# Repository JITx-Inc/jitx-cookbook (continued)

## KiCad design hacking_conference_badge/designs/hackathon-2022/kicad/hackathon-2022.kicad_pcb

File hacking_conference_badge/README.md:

# Hacking Conference Badge

This recipe serves as a playground for you to learn JITX while working on a functional PCB design. You’ll use the electronic conference badge template design in this folder to design your own electronic badge.

This template is a fully functioning board with an RP2040 microcontroller, battery and USB power solution, and a number of peripheral input/output devices that you can use as part of your badge design. We can roughly separate the template badge into 2 parts - the subsystems that you won’t change, and those that you (likely) will change.

##### Won't Change

- MCU (RP2040)
- MCU supporting circuitry (flash, crystal, etc.)
- power system (USB, battery charger, battery port, power switch)

##### Will Change

- RGB LED array
- solid color LED array
- potentiometers (dials/knobs)
- key-matrix array (buttons)
- Speaker
- TOF sensor (distance sensor)
- WS2816 array (addressable RGB LEDs)

### How The Badge Works

At this point, you should have forked/cloned this repo board, updated/inited submodules, and opened this folder/project in JITX VSCode. Make sure you're running the latest JITX version in VSCode.

The main design of the board is in `main.stanza`, open that in JITX VSCode and press "Ctrl+Enter" to build the board.

##### The Code

Briefly, let's go through the code.

The top level module is `public pcb-module hacking_conference_badge_module :`

Here, we instantiate and connect everything that will be part of our board.

`usb` - the USB connector
`battery` - the JST connector for the LiPo battery
`sw` - the power switch in series with the BQ2407 battery charger
`ld` - the LDO power/voltage regulator that converts voltage from the battery charger output to 2.8V for the RP2040 and other peripherals to run off of
`rpi` - the RP2040 microcontroller -> the brains/compute of the board
`led-drive` - the LED driver -> this accepts commands over I2C and turns the attached LEDs on/off. Notice that the RGB LEDs on the top left of the board are connected to this with 3 connections each - that is 1 for Red, 1 for green, and 1 for blue
`led-driver-shifter` - logic level shifter for the LED-driver. The LED-driver logic is running at its input power (~4.2V) whereas the RP2040 logic is running at 2.8V. This driver shifter shifts between those voltage levels so the LED-driver and RP2040 can talk to each other
`en-sw` - there are two of these which turn on and off a bank of single-color LEDs
`rgb-grid` - grid of RGB LEDs connected to the LED-driver
`amp` - this is the audio amplifier and speaker submodule
`knobs` - knobs/dials/potentiometers you can read directly with the RP2040 and use to do arbitrary things
`tof` - time of flight distance sensor, talks to RP2040 with I2C
`indicator-led-array` - array of WS2816 RGB addressable LEDs
`geom(NET)` - these are ground and power plane/pours
`power-net-class` - setting the trace width for various nets in the design
`run-design` - this compiles the board, or it runs checks on the board (depending on arguments)

##### Happy Hacking!

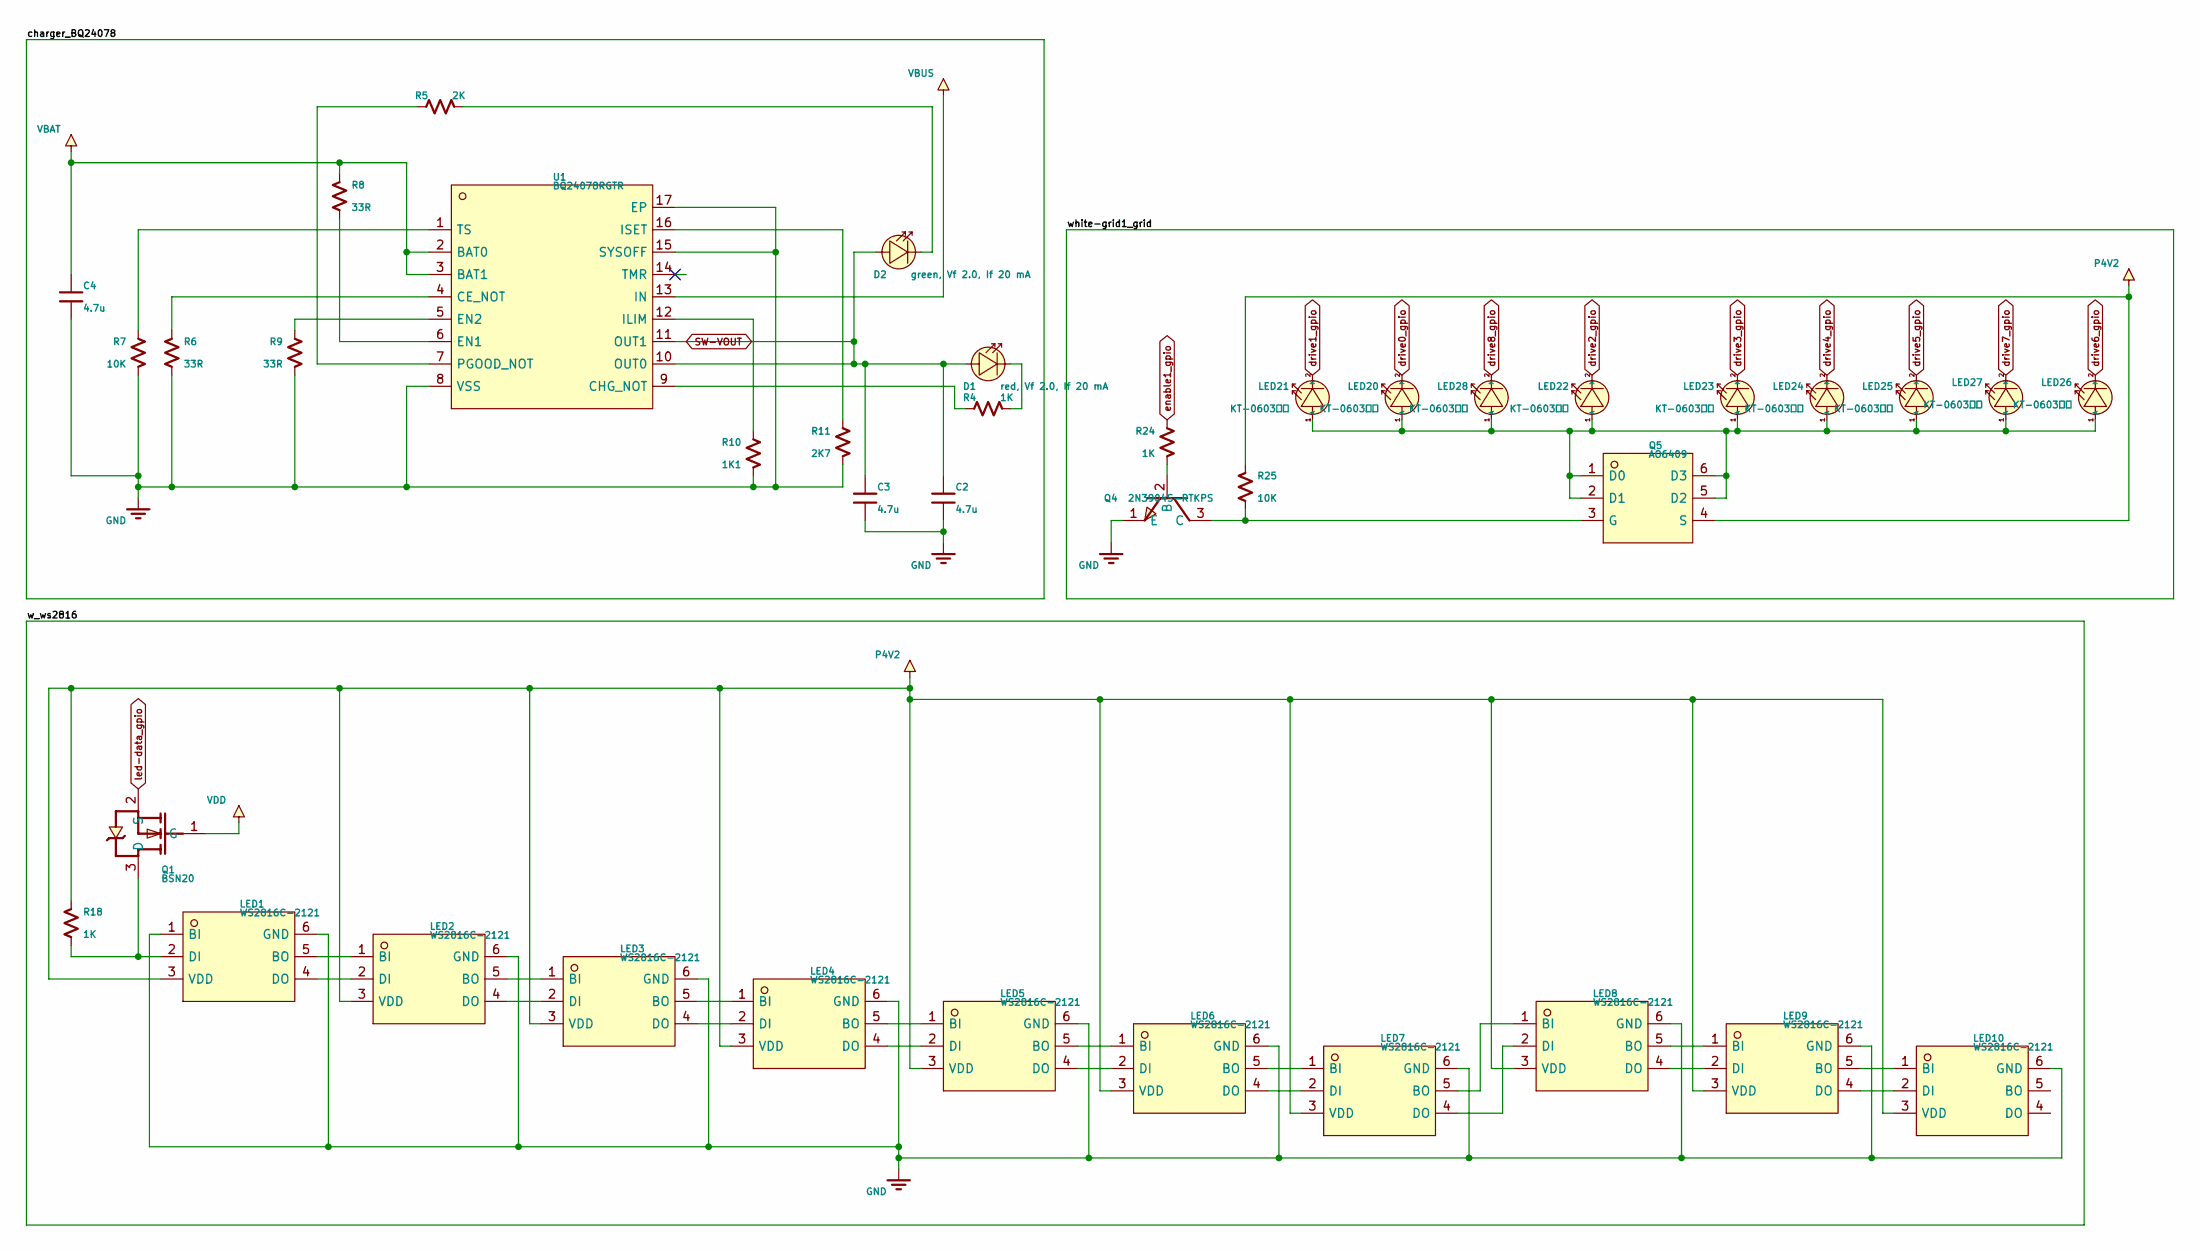
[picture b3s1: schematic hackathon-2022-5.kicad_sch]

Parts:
C2, C3, C4: 4.7u; Pkg0402; MPN 0402YD475MAT2A
D1: red, Vf 2.0, If 20 mA; Pkg0603; MPN red, Vf 2.0, If 20 mA
D2: green, Vf 2.0, If 20 mA; Pkg0603; MPN green, Vf 2.0, If 20 mA
LED1, LED2, LED3, LED4, LED5, LED6, LED7, LED8, LED9, LED10: WS2816C-2121; LED_SMD_6P_L2_2_W2_2_TL_1; MPN WS2816C-2121; LCSC C965561
LED20, LED21, LED22, LED23, LED24, LED25, LED26, LED27, LED28: KT-0603白灯; LED0603_R_RD_WHITE; MPN KT-0603白灯; LCSC C2290
Q1: BSN20; SOT_23_3_L2_9_W1_6_P1_90_LS2_8_BR; MPN BSN20; LCSC C116157
Q4: 2N3904S-RTKPS; SOT_23_3_L2_9_W1_3_P1_90_LS2_4_TR; MPN 2N3904S-RTKPS; LCSC C18536
Q5: AO6409; TSOP_6_L3_0_W1_5_P0_95_LS2_8_BR; MPN AO6409; LCSC C115833
R4: 1K; Pkg0402_6
R5: 2K; Pkg0402_6
R6, R8, R9: 33R; Pkg0402_6
R7: 10K; Pkg0402_6
R10: 1K1; Pkg0402_4; MPN RT0402DRE071K1L
R11: 2K7; Pkg0402_1; MPN RK73B1ERTTP272J
R18: 1K; Pkg0402_4; MPN RT0402BRB071KL
R24: 1K; Pkg0402_1; MPN SG73P1EWTTP1001F
R25: 10K; Pkg0402_1; MPN RC1005F103CS
U1: BQ24078RGTR; VQFN_16_L3_0_W3_0_P0_50_BL_EP; MPN BQ24078RGTR; LCSC C473396

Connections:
GND: C2.2, C3.2, C4.2, LED1.1 (BI), LED1.6 (GND), LED2.6 (GND), LED3.6 (GND), LED4.6 (GND), LED5.6 (GND), LED6.6 (GND), LED7.6 (GND), LED8.6 (GND), LED9.6 (GND), LED10.6 (GND), Q4.1 (E), R6.1, R7.2, R9.2, R10.2, R11.2, U1.8 (VSS), U1.15 (SYSOFF), U1.17 (EP); also elsewhere on the board
unnamed: D1.c, R4.2
unnamed: D2.c, R5.2
unnamed: LED1.5 (BO), LED2.1 (BI)
unnamed: LED1.2 (DI), Q1.3 (D), R18.1
unnamed: LED1.4 (DO), LED2.2 (DI)
unnamed: LED2.5 (BO), LED3.1 (BI)
unnamed: LED2.4 (DO), LED3.2 (DI)
unnamed: LED3.5 (BO), LED4.1 (BI)
unnamed: LED3.4 (DO), LED4.2 (DI)
unnamed: LED4.5 (BO), LED5.1 (BI)
unnamed: LED4.4 (DO), LED5.2 (DI)
unnamed: LED5.5 (BO), LED6.1 (BI)
unnamed: LED5.4 (DO), LED6.2 (DI)
unnamed: LED6.5 (BO), LED7.1 (BI)
unnamed: LED6.4 (DO), LED7.2 (DI)
unnamed: LED7.5 (BO), LED8.1 (BI)
unnamed: LED7.4 (DO), LED8.2 (DI)
unnamed: LED8.5 (BO), LED9.1 (BI)
unnamed: LED8.4 (DO), LED9.2 (DI)
unnamed: LED9.5 (BO), LED10.1 (BI)
unnamed: LED9.4 (DO), LED10.2 (DI)
unnamed: LED20.1 (A), LED21.1 (A), LED22.1 (A), LED23.1 (A), LED24.1 (A), LED25.1 (A), LED26.1 (A), LED27.1 (A), LED28.1 (A), Q5.1 (D0), Q5.2 (D1), Q5.5 (D2), Q5.6 (D3)
unnamed: Q4.2 (B), R24.2
unnamed: Q4.3 (C), Q5.3 (G), R25.1
unnamed: R6.2, U1.4 (CE_NOT)
unnamed: R4.1, U1.9 (CHG_NOT)
unnamed: R8.1, U1.6 (EN1)
unnamed: R9.1, U1.5 (EN2)
unnamed: R10.1, U1.12 (ILIM)
unnamed: R11.1, U1.16 (ISET)
unnamed: R5.1, U1.7 (PGOOD_NOT)
unnamed: R7.1, U1.1 (TS)
P4V2: LED1.3 (VDD), LED2.3 (VDD), LED3.3 (VDD), LED4.3 (VDD), LED5.3 (VDD), LED6.3 (VDD), LED7.3 (VDD), LED8.3 (VDD), LED9.3 (VDD), LED10.3 (VDD), Q5.4 (S), R18.2, R25.2; also elsewhere on the board
SW-VOUT: C2.1, C3.1, D1.a, D2.a, U1.10 (OUT0), U1.11 (OUT1); also elsewhere on the board
VBAT: C4.1, R8.2, U1.2 (BAT0), U1.3 (BAT1); also elsewhere on the board
VBUS: U1.13 (IN); also elsewhere on the board
VDD: Q1.1 (G); also elsewhere on the board
drive0_gpio: LED20.2 (K); also elsewhere on the board
drive1_gpio: LED21.2 (K); also elsewhere on the board
drive2_gpio: LED22.2 (K); also elsewhere on the board
drive3_gpio: LED23.2 (K); also elsewhere on the board
drive4_gpio: LED24.2 (K); also elsewhere on the board
drive5_gpio: LED25.2 (K); also elsewhere on the board
drive6_gpio: LED26.2 (K); also elsewhere on the board
drive7_gpio: LED27.2 (K); also elsewhere on the board
drive8_gpio: LED28.2 (K); also elsewhere on the board
enable1_gpio: R24.1; also elsewhere on the board
led-data_gpio: Q1.2 (S); also elsewhere on the board

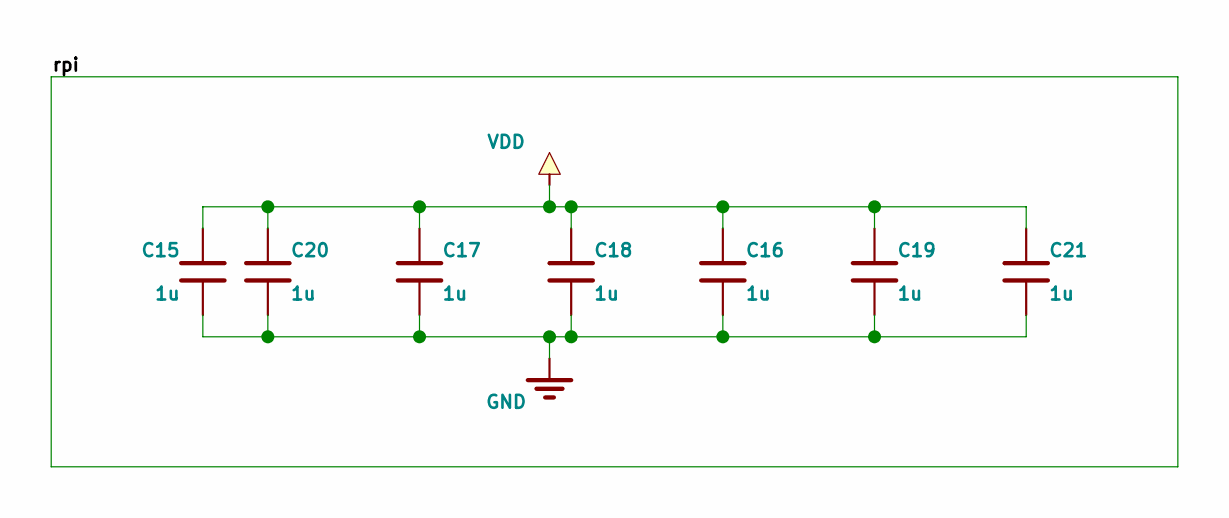
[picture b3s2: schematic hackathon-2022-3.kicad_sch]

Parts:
C15, C16, C17, C18, C19, C20, C21: 1u; Pkg0402_2; MPN LMK105C6105KV-F

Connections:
GND: C15.1, C16.2, C17.2, C18.2, C19.2, C20.2, C21.2; also elsewhere on the board
VDD: C15.2, C16.1, C17.1, C18.1, C19.1, C20.1, C21.1; also elsewhere on the board

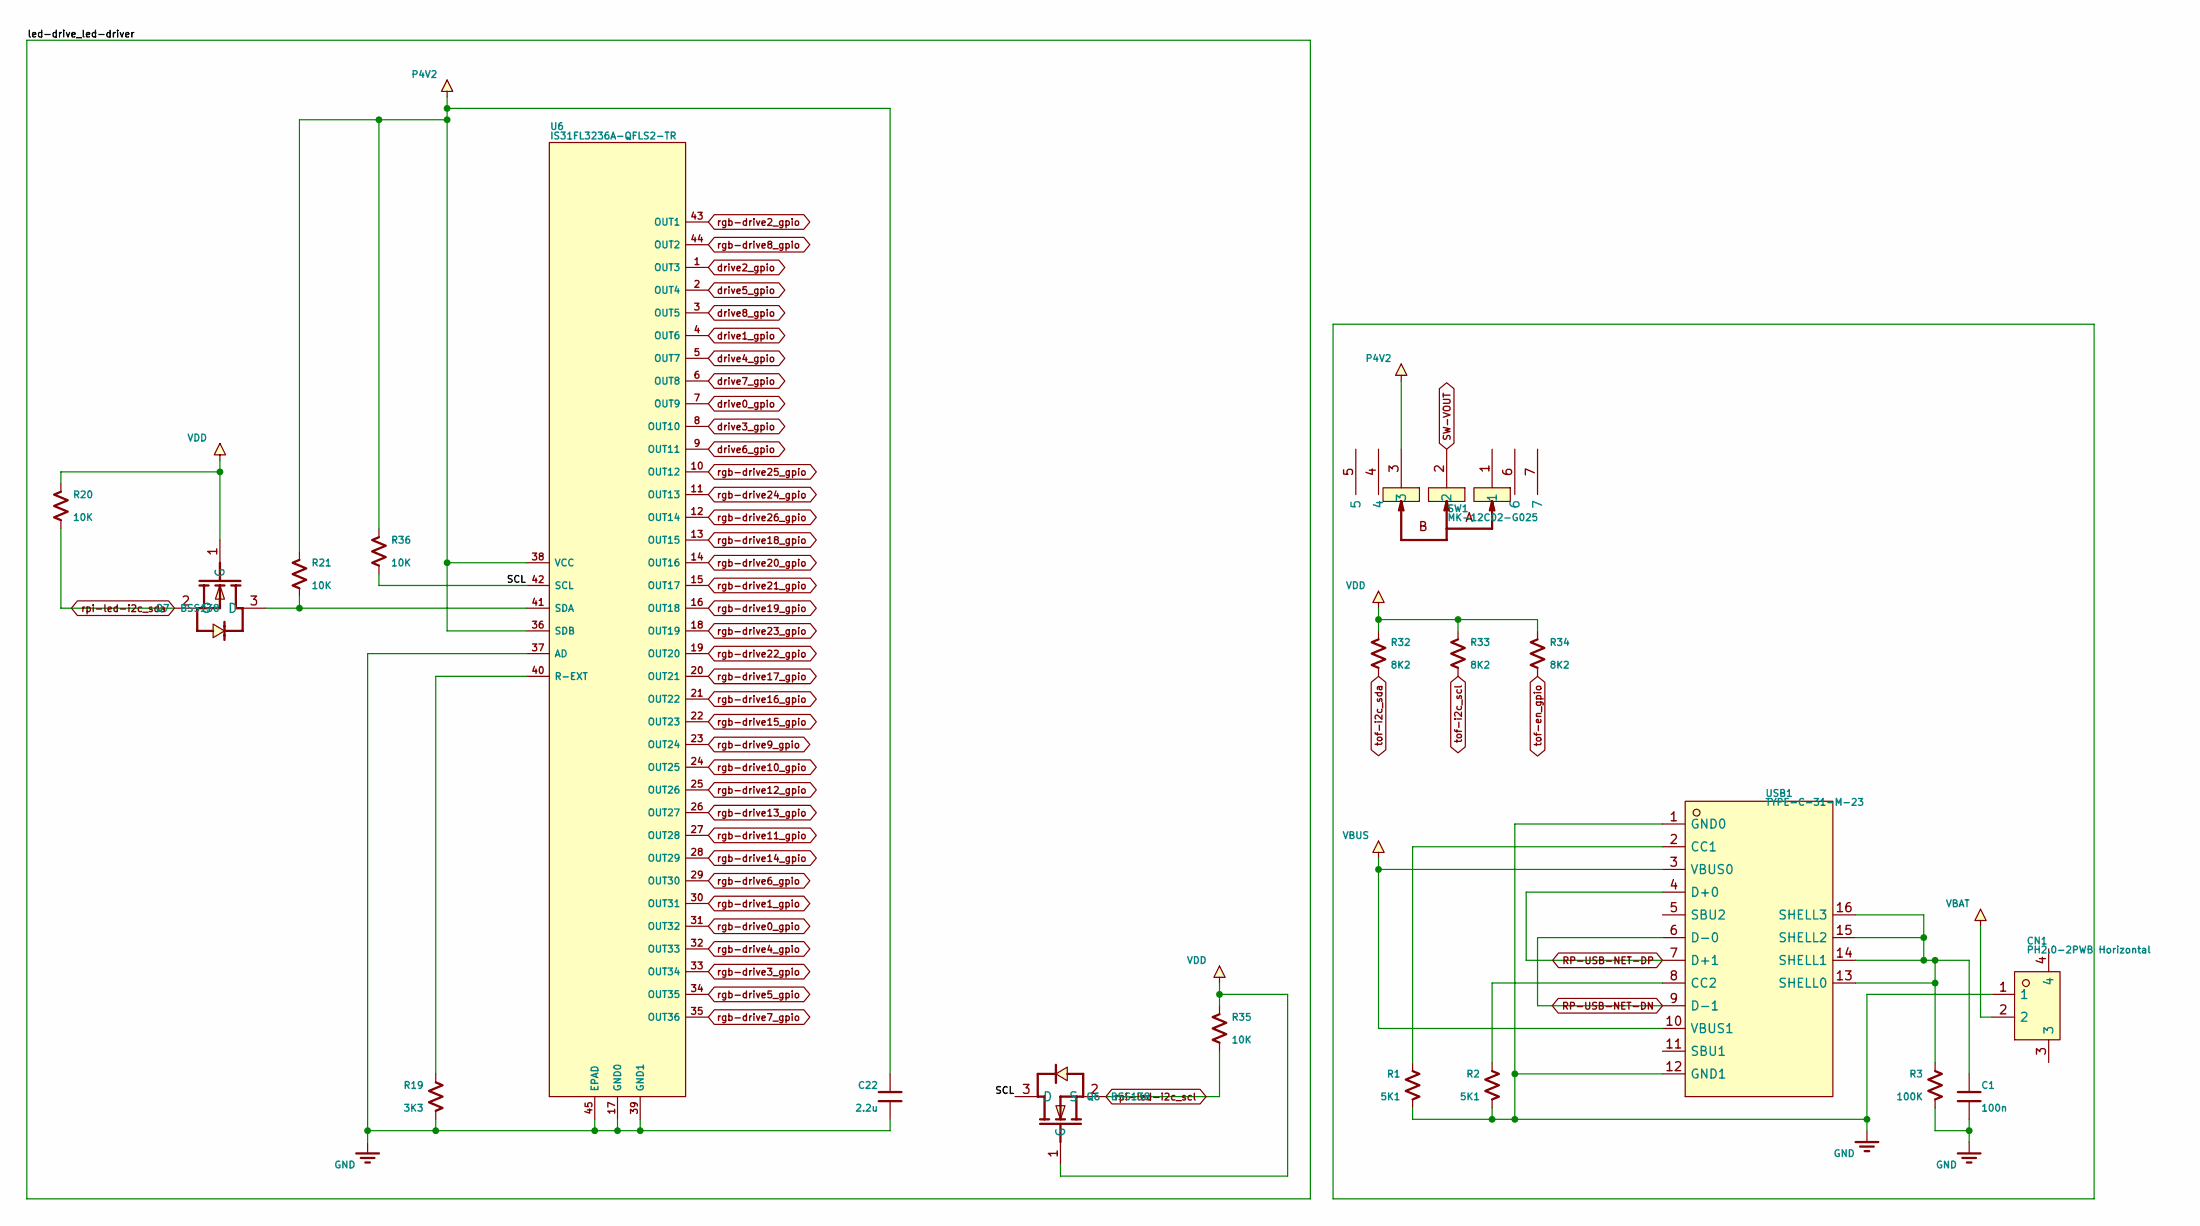
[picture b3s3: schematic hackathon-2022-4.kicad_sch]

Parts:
C1: 100n; Pkg0402_2; MPN CL05B104KA5NNNC
C22: 2.2u; Pkg0402_5; MPN C1005X5R1E225K050BE
CN1: PH2.0-2PWB Horizontal; CONN_SMD_2P_P2_00_PH2_0_SPWB; MPN PH2.0-2PWB Horizontal; LCSC C47647
Q6, Q7: BSS138; SOT_23_3_L2_9_W1_3_P1_90_LS2_4_BR; MPN BSS138; LCSC C713688
R1, R2: 5K1; Pkg0402_1; MPN ERJ-2GEJ512X
R3: 100K; Pkg0402_1; MPN RK73B1ERTTP104J
R19: 3K3; Pkg0402_1; MPN RK73H1ERTTP3301D
R20, R21, R35, R36: 10K; Pkg0402_1; MPN ESR01MZPJ103
R32, R33, R34: 8K2; Pkg0402_3; MPN CR0402AJW-822GLF
SW1: MK-12C02-G025; SW_SMD_MK_12C02_G025; MPN MK-12C02-G025; LCSC C778186
U6: IS31FL3236A-QFLS2-TR; C246443; MPN IS31FL3236A-QFLS2-TR; LCSC C246443
USB1: TYPE-C-31-M-23; USB_C_SMD_TYPE_C_31_M_23; MPN TYPE-C-31-M-23; LCSC C530613

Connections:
/4: led-drive_u/SCL: Q6.3 (D), R36.1, U6.42 (SCL)
GND: C1.2, C22.1, CN1.1, R1.2, R2.2, R3.2, R19.2, U6.17 (GND0), U6.37 (AD), U6.39 (GND1), U6.45 (EPAD), USB1.1 (GND0), USB1.12 (GND1); also elsewhere on the board
unnamed: Q7.3 (D), R21.1, U6.41 (SDA)
unnamed: R19.1, U6.40 (R-EXT)
unnamed: R1.1, USB1.2 (CC1)
unnamed: R2.1, USB1.8 (CC2)
unnamed: C1.1, R3.1, USB1.13 (SHELL0), USB1.14 (SHELL1), USB1.15 (SHELL2), USB1.16 (SHELL3)
P4V2: C22.2, R21.2, R36.2, SW1.3, U6.36 (SDB), U6.38 (VCC); also elsewhere on the board
RP-USB-NET-DN: USB1.6 (D-0), USB1.9 (D-1); also elsewhere on the board
RP-USB-NET-DP: USB1.4 (D+0), USB1.7 (D+1); also elsewhere on the board
SW-VOUT: SW1.2; also elsewhere on the board
VBAT: CN1.2; also elsewhere on the board
VBUS: USB1.3 (VBUS0), USB1.10 (VBUS1); also elsewhere on the board
VDD: Q6.1 (G), Q7.1 (G), R20.2, R32.2, R33.2, R34.2, R35.2; also elsewhere on the board
drive0_gpio: U6.7 (OUT9); also elsewhere on the board
drive1_gpio: U6.4 (OUT6); also elsewhere on the board
drive2_gpio: U6.1 (OUT3); also elsewhere on the board
drive3_gpio: U6.8 (OUT10); also elsewhere on the board
drive4_gpio: U6.5 (OUT7); also elsewhere on the board
drive5_gpio: U6.2 (OUT4); also elsewhere on the board
drive6_gpio: U6.9 (OUT11); also elsewhere on the board
drive7_gpio: U6.6 (OUT8); also elsewhere on the board
drive8_gpio: U6.3 (OUT5); also elsewhere on the board
rgb-drive0_gpio: U6.31 (OUT32); also elsewhere on the board
rgb-drive1_gpio: U6.30 (OUT31); also elsewhere on the board
rgb-drive2_gpio: U6.43 (OUT1); also elsewhere on the board
rgb-drive3_gpio: U6.33 (OUT34); also elsewhere on the board
rgb-drive4_gpio: U6.32 (OUT33); also elsewhere on the board
rgb-drive5_gpio: U6.34 (OUT35); also elsewhere on the board
rgb-drive6_gpio: U6.29 (OUT30); also elsewhere on the board
rgb-drive7_gpio: U6.35 (OUT36); also elsewhere on the board
rgb-drive8_gpio: U6.44 (OUT2); also elsewhere on the board
rgb-drive9_gpio: U6.23 (OUT24); also elsewhere on the board
rgb-drive10_gpio: U6.24 (OUT25); also elsewhere on the board
rgb-drive11_gpio: U6.27 (OUT28); also elsewhere on the board
rgb-drive12_gpio: U6.25 (OUT26); also elsewhere on the board
rgb-drive13_gpio: U6.26 (OUT27); also elsewhere on the board
rgb-drive14_gpio: U6.28 (OUT29); also elsewhere on the board
rgb-drive15_gpio: U6.22 (OUT23); also elsewhere on the board
rgb-drive16_gpio: U6.21 (OUT22); also elsewhere on the board
rgb-drive17_gpio: U6.20 (OUT21); also elsewhere on the board
rgb-drive18_gpio: U6.13 (OUT15); also elsewhere on the board
rgb-drive19_gpio: U6.16 (OUT18); also elsewhere on the board
rgb-drive20_gpio: U6.14 (OUT16); also elsewhere on the board
rgb-drive21_gpio: U6.15 (OUT17); also elsewhere on the board
rgb-drive22_gpio: U6.19 (OUT20); also elsewhere on the board
rgb-drive23_gpio: U6.18 (OUT19); also elsewhere on the board
rgb-drive24_gpio: U6.11 (OUT13); also elsewhere on the board
rgb-drive25_gpio: U6.10 (OUT12); also elsewhere on the board
rgb-drive26_gpio: U6.12 (OUT14); also elsewhere on the board
rpi-led-i2c_scl: Q6.2 (S), R35.1; also elsewhere on the board
rpi-led-i2c_sda: Q7.2 (S), R20.1; also elsewhere on the board
tof-en_gpio: R34.1; also elsewhere on the board
tof-i2c_scl: R33.1; also elsewhere on the board
tof-i2c_sda: R32.1; also elsewhere on the board

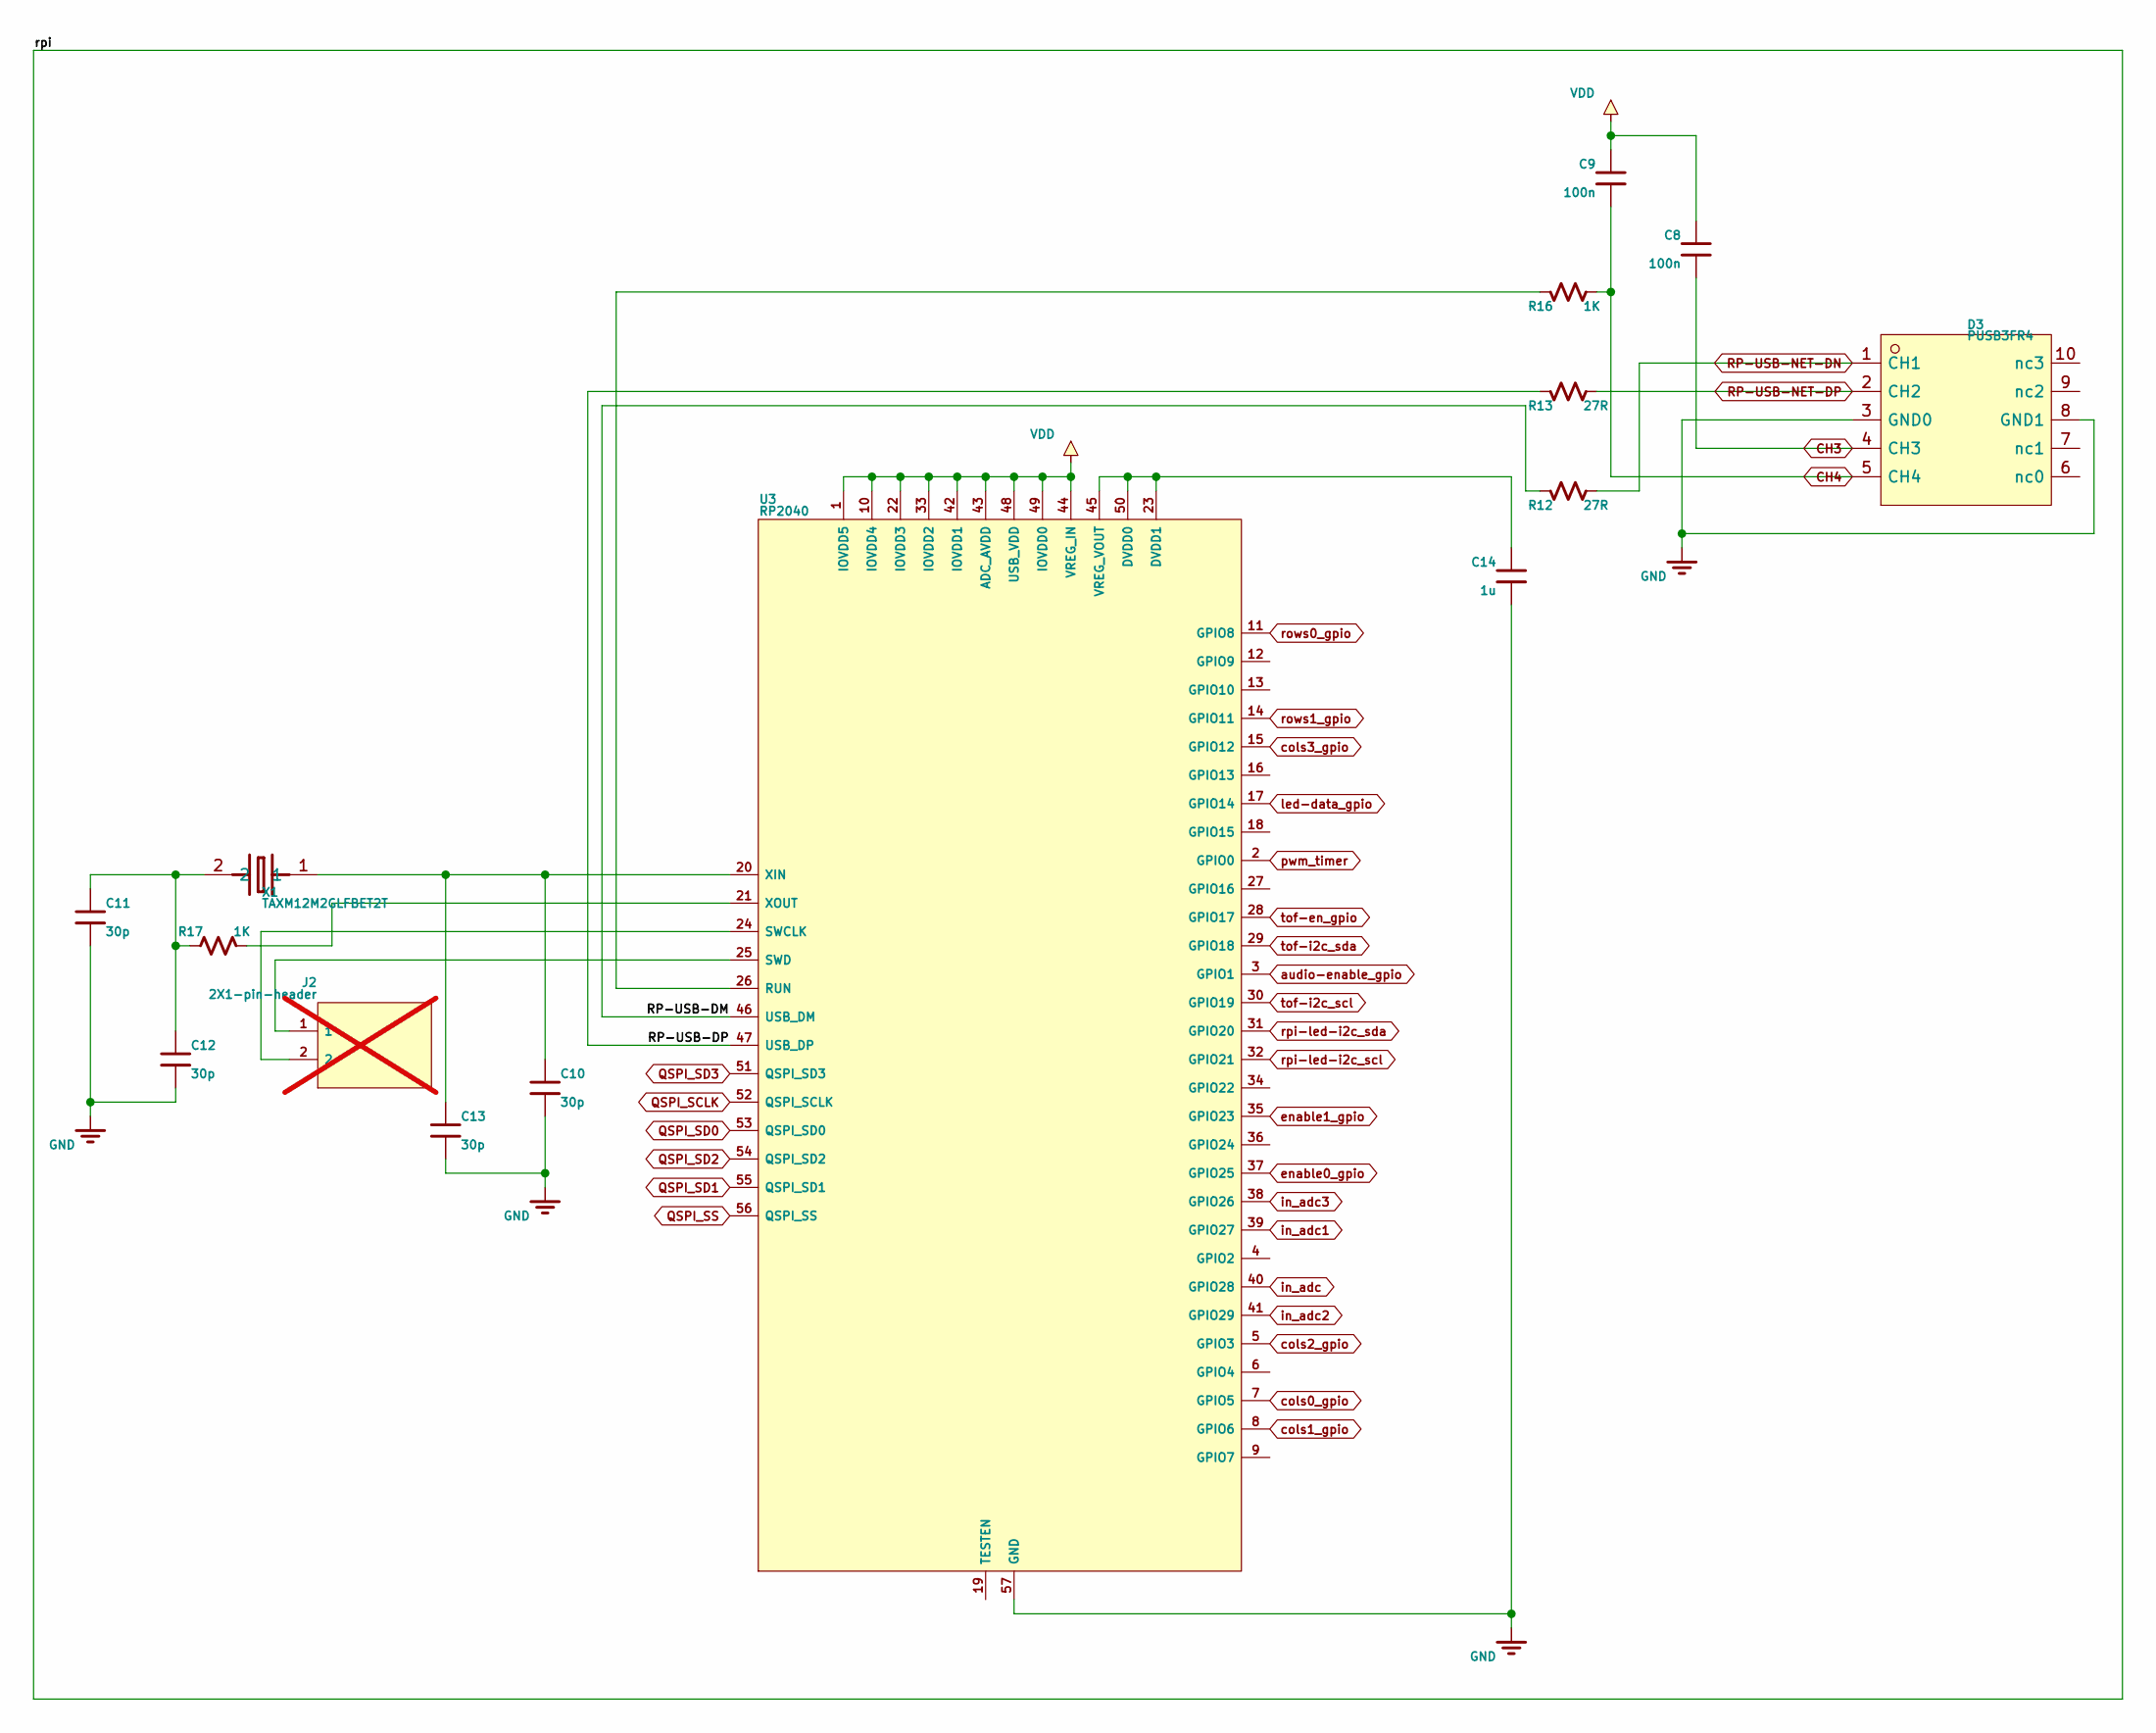
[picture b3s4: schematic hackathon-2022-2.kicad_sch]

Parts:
C8, C9: 100n; Pkg0402_2; MPN CL05B104KA5NNNC
C10, C11, C12, C13: 30p; Pkg0402_2; MPN CC0402JRNPO9BN300
C14: 1u; Pkg0402_2; MPN LMK105C6105KV-F
D3: PUSB3FR4; DFN2510A_10_L2_5_W1_0_P0_50_BL; MPN PUSB3FR4; LCSC C294620
J2: 2X1-pin-header; PIN_GRID; MPN 2X1-pin-header; not fitted
R12, R13: 27R; Pkg0402_1; MPN ERJ-U02F27R0X
R16, R17: 1K; Pkg0402_4; MPN RT0402BRB071KL
U3: RP2040; C2040; MPN RP2040
X1: TAXM12M2GLFBET2T; HC_49S_L11_4_W4_8; MPN TAXM12M2GLFBET2T; LCSC C111117

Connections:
/2: rpi_mcu/RP-USB-DM: R12.2, U3.46 (USB_DM)
/2: rpi_mcu/RP-USB-DP: R13.2, U3.47 (USB_DP)
CH3: C8.1, D3.4 (CH3); also elsewhere on the board
CH4: C9.1, D3.5 (CH4), R16.1; also elsewhere on the board
GND: C10.2, C11.2, C12.2, C13.2, C14.1, D3.3 (GND0), D3.8 (GND1), U3.57 (GND); also elsewhere on the board
unnamed: C11.1, C12.1, R17.1, X1.2
unnamed: C14.2, U3.23 (DVDD1), U3.45 (VREG_VOUT), U3.50 (DVDD0)
unnamed: R16.2, U3.26 (RUN)
unnamed: J2.2, U3.24 (SWCLK)
unnamed: J2.1, U3.25 (SWD)
unnamed: C10.1, C13.1, U3.20 (XIN), X1.1
unnamed: R17.2, U3.21 (XOUT)
QSPI_SCLK: U3.52 (QSPI_SCLK); also elsewhere on the board
QSPI_SD0: U3.53 (QSPI_SD0); also elsewhere on the board
QSPI_SD1: U3.55 (QSPI_SD1); also elsewhere on the board
QSPI_SD2: U3.54 (QSPI_SD2); also elsewhere on the board
QSPI_SD3: U3.51 (QSPI_SD3); also elsewhere on the board
QSPI_SS: U3.56 (QSPI_SS); also elsewhere on the board
RP-USB-NET-DN: D3.1 (CH1), R12.1; also elsewhere on the board
RP-USB-NET-DP: D3.2 (CH2), R13.1; also elsewhere on the board
VDD: C8.2, C9.2, U3.1 (IOVDD5), U3.10 (IOVDD4), U3.22 (IOVDD3), U3.33 (IOVDD2), U3.42 (IOVDD1), U3.43 (ADC_AVDD), U3.44 (VREG_IN), U3.48 (USB_VDD), U3.49 (IOVDD0); also elsewhere on the board
audio-enable_gpio: U3.3 (GPIO1); also elsewhere on the board
cols0_gpio: U3.7 (GPIO5); also elsewhere on the board
cols1_gpio: U3.8 (GPIO6); also elsewhere on the board
cols2_gpio: U3.5 (GPIO3); also elsewhere on the board
cols3_gpio: U3.15 (GPIO12); also elsewhere on the board
enable0_gpio: U3.37 (GPIO25); also elsewhere on the board
enable1_gpio: U3.35 (GPIO23); also elsewhere on the board
in_adc: U3.40 (GPIO28); also elsewhere on the board
in_adc1: U3.39 (GPIO27); also elsewhere on the board
in_adc2: U3.41 (GPIO29); also elsewhere on the board
in_adc3: U3.38 (GPIO26); also elsewhere on the board
led-data_gpio: U3.17 (GPIO14); also elsewhere on the board
pwm_timer: U3.2 (GPIO0); also elsewhere on the board
rows0_gpio: U3.11 (GPIO8); also elsewhere on the board
rows1_gpio: U3.14 (GPIO11); also elsewhere on the board
rpi-led-i2c_scl: U3.32 (GPIO21); also elsewhere on the board
rpi-led-i2c_sda: U3.31 (GPIO20); also elsewhere on the board
tof-en_gpio: U3.28 (GPIO17); also elsewhere on the board
tof-i2c_scl: U3.30 (GPIO19); also elsewhere on the board
tof-i2c_sda: U3.29 (GPIO18); also elsewhere on the board

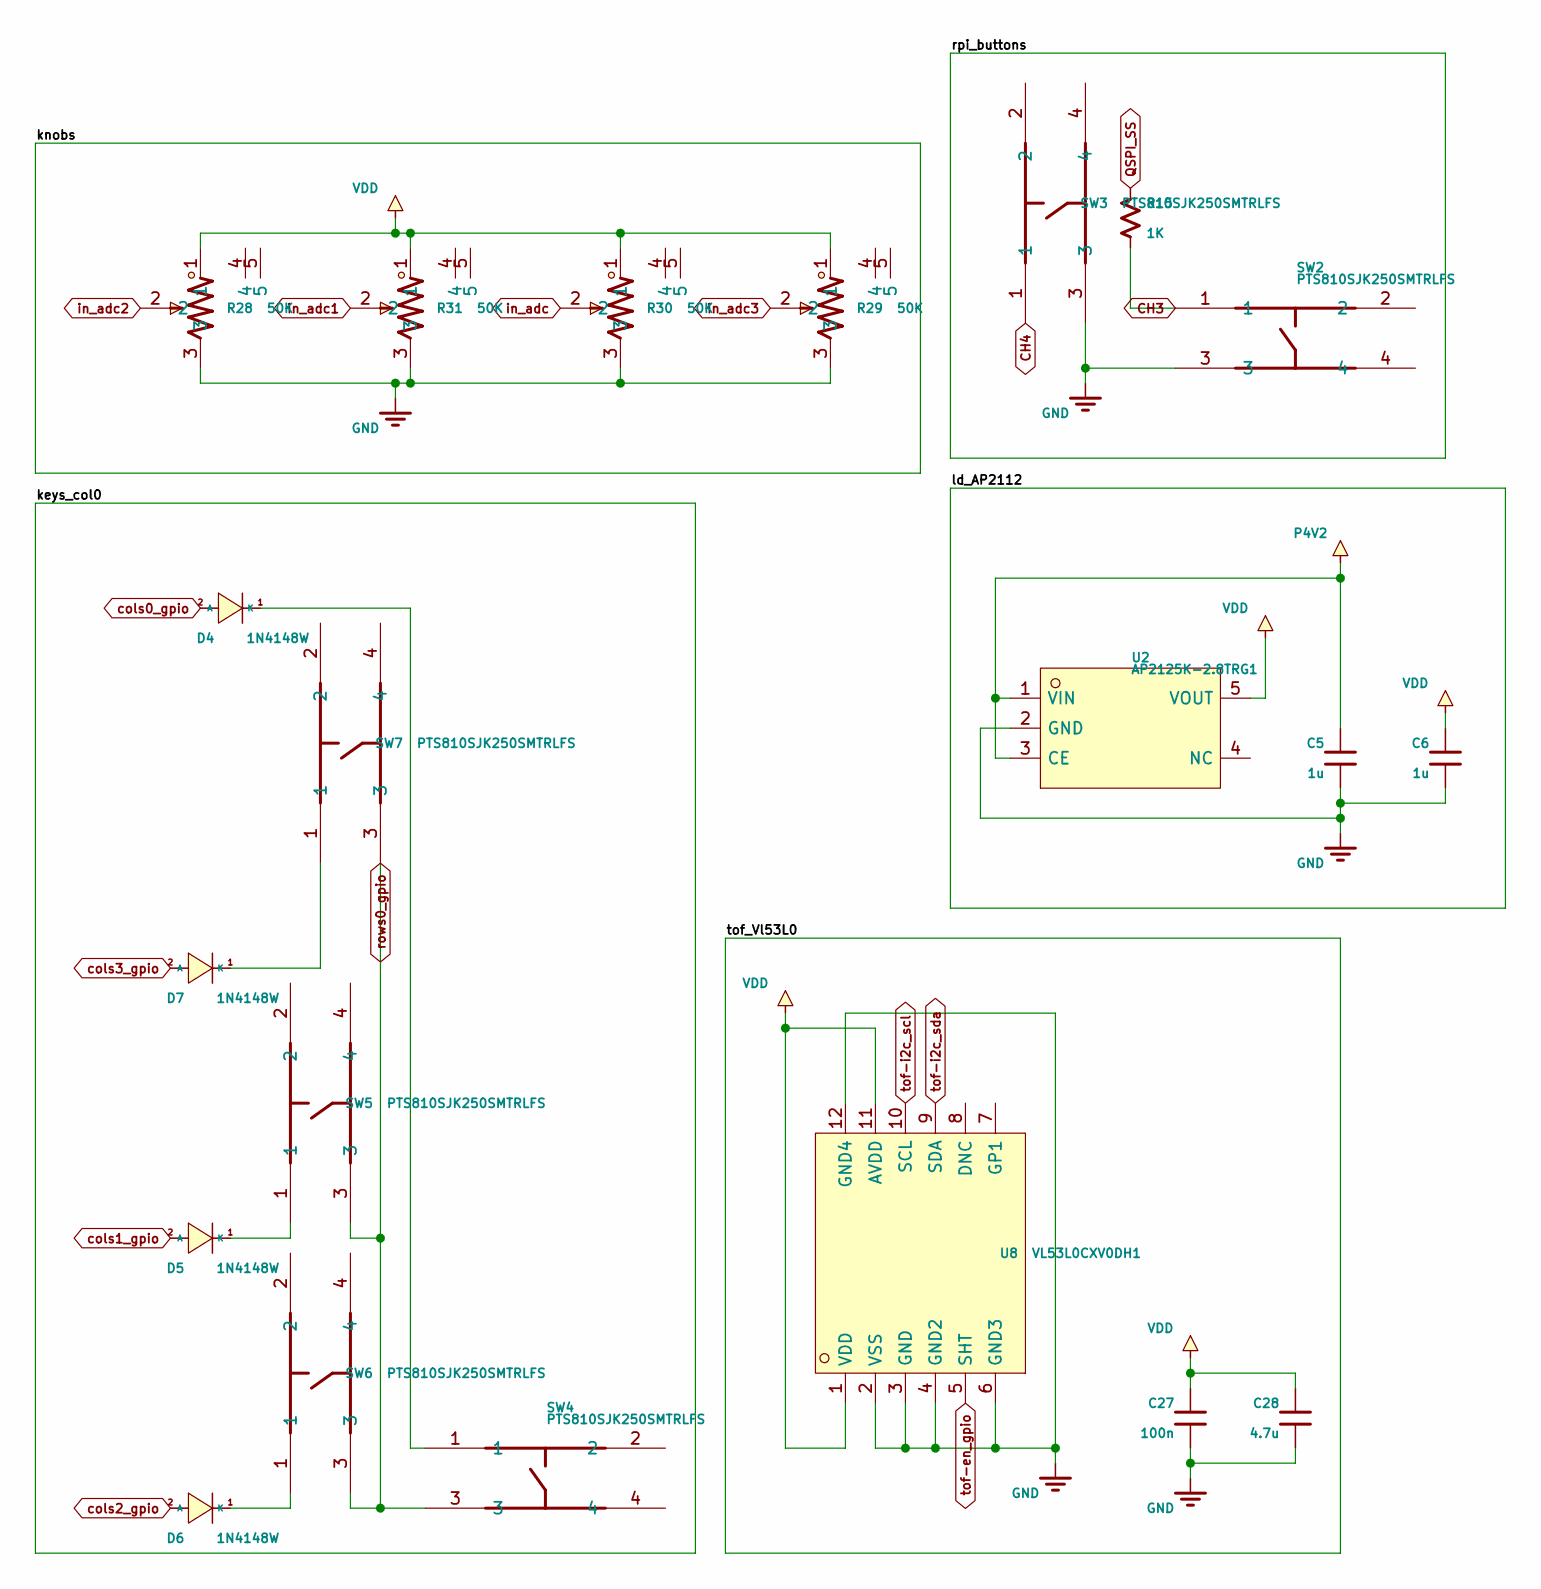
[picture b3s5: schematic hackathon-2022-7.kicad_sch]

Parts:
C5, C6: 1u; Pkg0402_2; MPN LMK105C6105KV-F
C27: 100n; Pkg0402_2; MPN CL05B104KA5NNNC
C28: 4.7u; Pkg0402_5; MPN C1005X5R1A475K050BE
D4: 1N4148W; SOD_123F_L2_7_W1_6_LS3_8_RD; MPN 1N4148W; LCSC C81598
D5: 1N4148W; SOD_123F_L2_7_W1_6_LS3_8_RD_5; MPN 1N4148W; LCSC C81598
D6: 1N4148W; SOD_123F_L2_7_W1_6_LS3_8_RD_3; MPN 1N4148W; LCSC C81598
D7: 1N4148W; SOD_123F_L2_7_W1_6_LS3_8_RD_1; MPN 1N4148W; LCSC C81598
R15: 1K; Pkg0402_4; MPN RT0402BRB071KL
R28, R29, R30, R31: 50K; RES_TH_RK09K1130AAU; MPN RK09K1130ACL; LCSC C470291
SW2: PTS810SJK250SMTRLFS; KEY_SMD_4P_L4_2_W3_2_P2_20_LS4_6_3; MPN PTS810SJK250SMTRLFS; LCSC C221896
SW3: PTS810SJK250SMTRLFS; KEY_SMD_4P_L4_2_W3_2_P2_20_LS4_6_9; MPN PTS810SJK250SMTRLFS; LCSC C221896
SW4: PTS810SJK250SMTRLFS; KEY_SMD_4P_L4_2_W3_2_P2_20_LS4_6_4; MPN PTS810SJK250SMTRLFS; LCSC C221896
SW5: PTS810SJK250SMTRLFS; KEY_SMD_4P_L4_2_W3_2_P2_20_LS4_6; MPN PTS810SJK250SMTRLFS; LCSC C221896
SW6: PTS810SJK250SMTRLFS; KEY_SMD_4P_L4_2_W3_2_P2_20_LS4_6_7; MPN PTS810SJK250SMTRLFS; LCSC C221896
SW7: PTS810SJK250SMTRLFS; KEY_SMD_4P_L4_2_W3_2_P2_20_LS4_6_5; MPN PTS810SJK250SMTRLFS; LCSC C221896
U2: AP2125K-2.8TRG1; SOT_23_5_L3_0_W1_7_P0_95_LS2_8_BR; MPN AP2125K-2.8TRG1; LCSC C176952
U8: VL53L0CXV0DH1; OPTO_SMD_12P_VL53L0CXV0DH_1; MPN VL53L0CXV0DH1; LCSC C91199

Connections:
CH3: R15.1, SW2.1; also elsewhere on the board
CH4: SW3.1; also elsewhere on the board
GND: C5.1, C6.1, C27.1, C28.1, R28.3, R29.3, R30.3, R31.3, SW2.3, SW3.3, U2.2 (GND), U8.2 (VSS), U8.3 (GND), U8.4 (GND2), U8.6 (GND3), U8.12 (GND4); also elsewhere on the board
unnamed: D4.1 (K), SW4.1
unnamed: D5.1 (K), SW5.1
unnamed: D6.1 (K), SW6.1
unnamed: D7.1 (K), SW7.1
P4V2: C5.2, U2.1 (VIN), U2.3 (CE); also elsewhere on the board
QSPI_SS: R15.2; also elsewhere on the board
VDD: C6.2, C27.2, C28.2, R28.1, R29.1, R30.1, R31.1, U2.5 (VOUT), U8.1 (VDD), U8.11 (AVDD); also elsewhere on the board
cols0_gpio: D4.2 (A); also elsewhere on the board
cols1_gpio: D5.2 (A); also elsewhere on the board
cols2_gpio: D6.2 (A); also elsewhere on the board
cols3_gpio: D7.2 (A); also elsewhere on the board
in_adc: R30.2; also elsewhere on the board
in_adc1: R31.2; also elsewhere on the board
in_adc2: R28.2; also elsewhere on the board
in_adc3: R29.2; also elsewhere on the board
rows0_gpio: SW4.3, SW5.3, SW6.3, SW7.3; also elsewhere on the board
tof-en_gpio: U8.5 (SHT); also elsewhere on the board
tof-i2c_scl: U8.10 (SCL); also elsewhere on the board
tof-i2c_sda: U8.9 (SDA); also elsewhere on the board
